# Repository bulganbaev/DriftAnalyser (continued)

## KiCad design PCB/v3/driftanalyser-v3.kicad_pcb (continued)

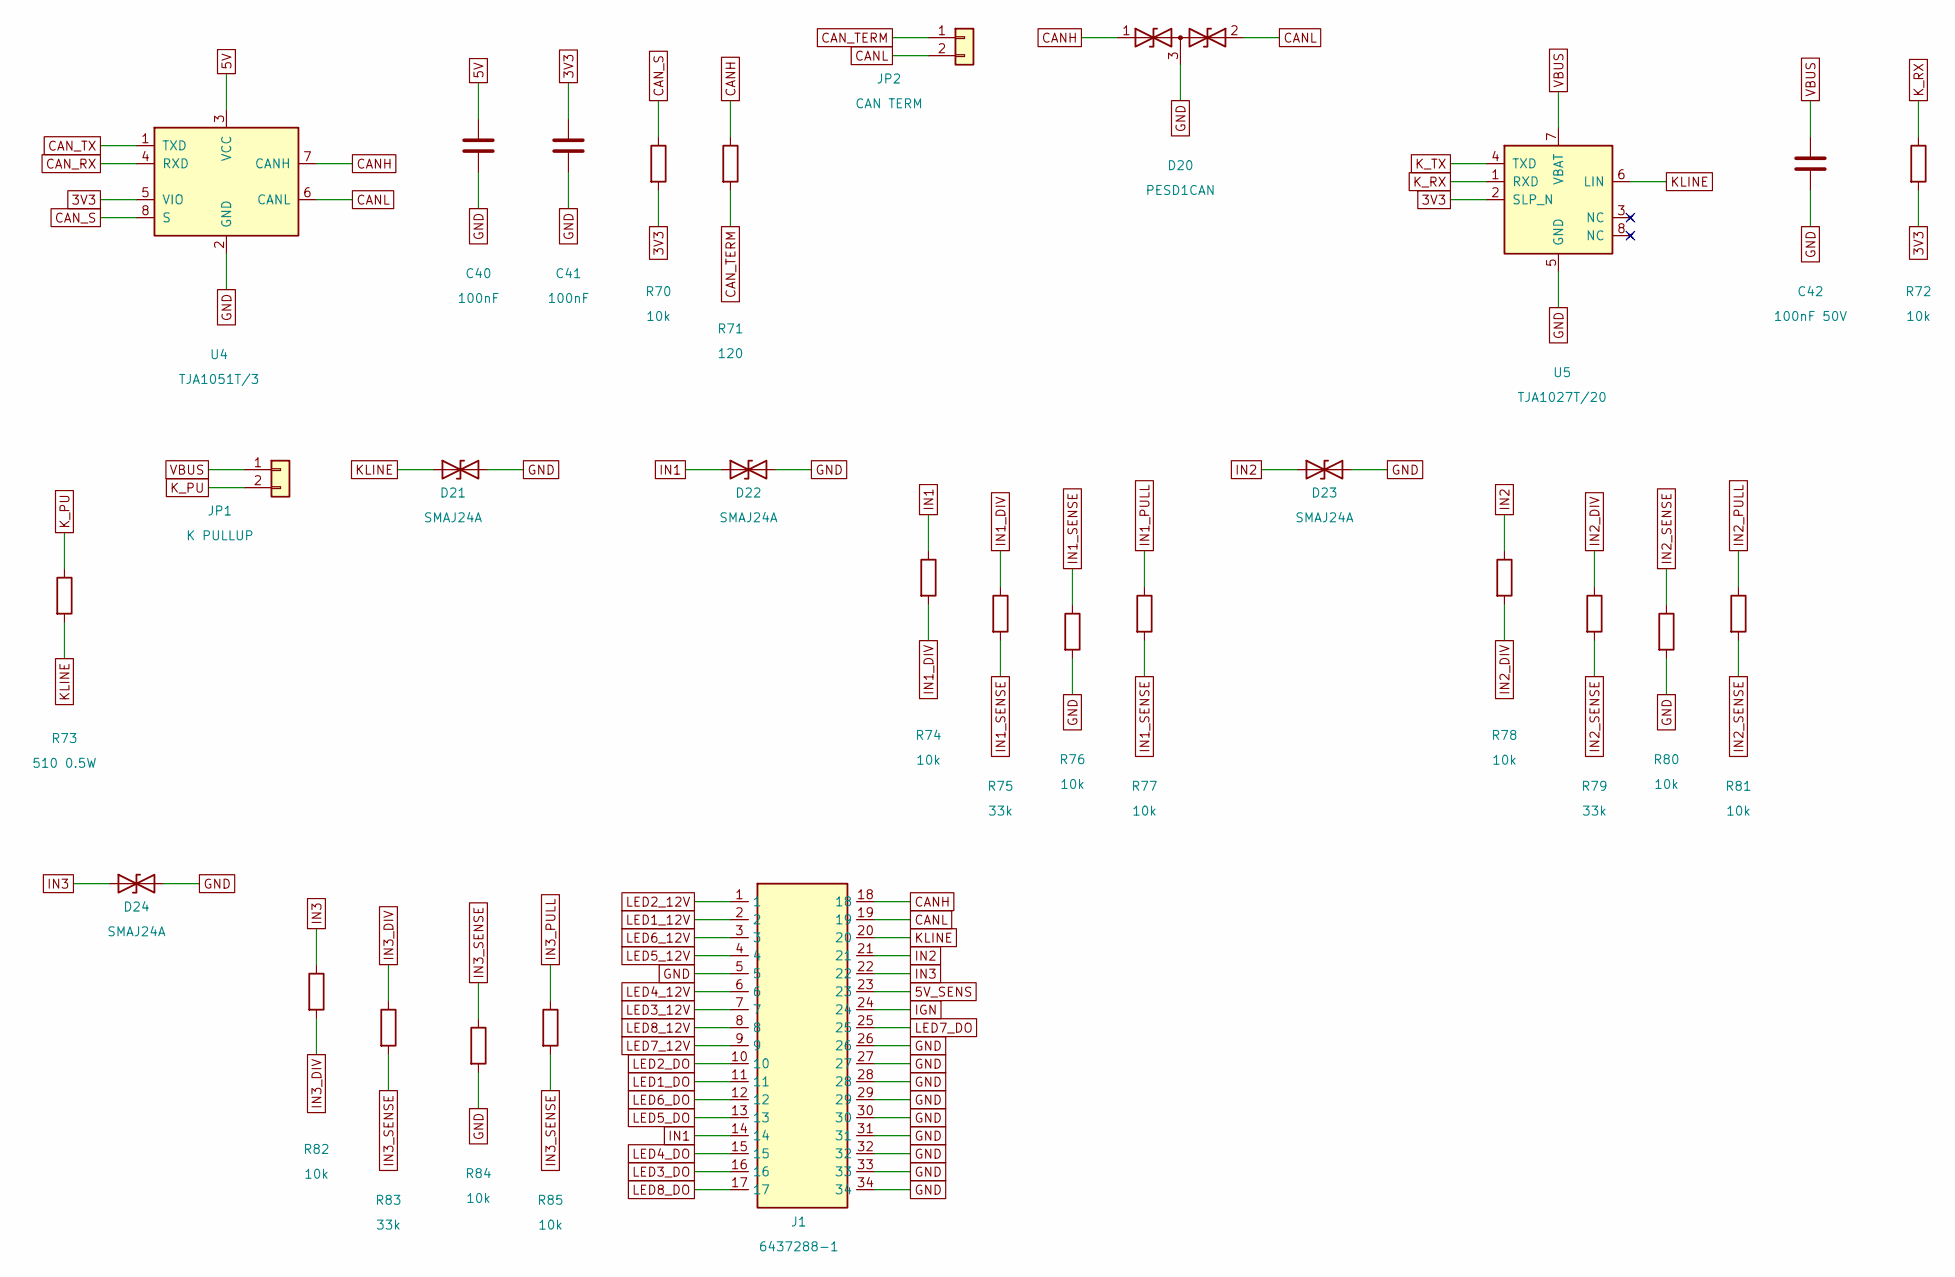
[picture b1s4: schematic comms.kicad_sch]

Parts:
C40, C41: 100nF; C_0603_1608Metric; MPN CC0603KRX7R9BB104; LCSC C14663
C42: 100nF 50V; C_0603_1608Metric; MPN CC0603KRX7R9BB104; LCSC C14663
D20: PESD1CAN; SOT-23; MPN PESD1CAN,215; LCSC C15771
D21, D22, D23, D24: SMAJ24A; D_SMA; MPN SMAJ24A; LCSC C148222
J1: 6437288-1; TE_6437288-1; MPN 6437288-1; LCSC C574787
JP1: K PULLUP; PinHeader_1x02_P2.54mm_Vertical; MPN PZ254V-11-02P; LCSC C492401
JP2: CAN TERM; PinHeader_1x02_P2.54mm_Vertical; MPN PZ254V-11-02P; LCSC C492401
R70, R72, R74, R76, R77, R78, R80, R81, R82, R84, R85: 10k; R_0603_1608Metric; MPN 0603WAF1002T5E; LCSC C25804
R71: 120; R_1206_3216Metric; MPN 1206W4F1200T5E; LCSC C17909
R73: 510 0.5W; R_2512_6332Metric; MPN FRC2512J511TS; LCSC C2934121
R75, R79, R83: 33k; R_0603_1608Metric; MPN 0603WAF3302T5E; LCSC C4216
U4: TJA1051T/3; SOIC-8_3.9x4.9mm_P1.27mm; MPN TJA1051T/3,118; LCSC C58988
U5: TJA1027T/20; SOIC-8_3.9x4.9mm_P1.27mm; MPN TJA1027T/20,118; LCSC C112994

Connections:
3V3: C41.1, R70.2, R72.2, U4.5 (VIO), U5.2 (SLP_N); also elsewhere on the board
5V: C40.1, U4.3 (VCC); also elsewhere on the board
5V_SENS: J1.23; also elsewhere on the board
CANH: D20.1 (A1), J1.18, R71.1, U4.7 (CANH)
CANL: D20.2 (A2), J1.19, JP2.2, U4.6 (CANL)
CAN_RX: U4.4 (RXD); also elsewhere on the board
CAN_S: R70.1, U4.8 (S); also elsewhere on the board
CAN_TERM: JP2.1, R71.2
CAN_TX: U4.1 (TXD); also elsewhere on the board
GND: C40.2, C41.2, C42.2, D20.3 (common), D21.2 (A2), D22.2 (A2), D23.2 (A2), D24.2 (A2), J1.5, J1.26, J1.27, J1.28, J1.29, J1.30, J1.31, J1.32, J1.33, J1.34, R76.2, R80.2, R84.2, U4.2 (GND), U5.5 (GND); also elsewhere on the board
IGN: J1.24; also elsewhere on the board
IN1: D22.1 (A1), J1.14, R74.1
IN1_DIV: R74.2, R75.1
IN1_PULL: R77.1; also elsewhere on the board
IN1_SENSE: R75.2, R76.1, R77.2; also elsewhere on the board
IN2: D23.1 (A1), J1.21, R78.1
IN2_DIV: R78.2, R79.1
IN2_PULL: R81.1; also elsewhere on the board
IN2_SENSE: R79.2, R80.1, R81.2; also elsewhere on the board
IN3: D24.1 (A1), J1.22, R82.1
IN3_DIV: R82.2, R83.1
IN3_PULL: R85.1; also elsewhere on the board
IN3_SENSE: R83.2, R84.1, R85.2; also elsewhere on the board
KLINE: D21.1 (A1), J1.20, R73.2, U5.6 (LIN)
K_PU: JP1.2, R73.1
K_RX: R72.1, U5.1 (RXD); also elsewhere on the board
K_TX: U5.4 (TXD); also elsewhere on the board
LED1_12V: J1.2; also elsewhere on the board
LED1_DO: J1.11; also elsewhere on the board
LED2_12V: J1.1; also elsewhere on the board
LED2_DO: J1.10; also elsewhere on the board
LED3_12V: J1.7; also elsewhere on the board
LED3_DO: J1.16; also elsewhere on the board
LED4_12V: J1.6; also elsewhere on the board
LED4_DO: J1.15; also elsewhere on the board
LED5_12V: J1.4; also elsewhere on the board
LED5_DO: J1.13; also elsewhere on the board
LED6_12V: J1.3; also elsewhere on the board
LED6_DO: J1.12; also elsewhere on the board
LED7_12V: J1.9; also elsewhere on the board
LED7_DO: J1.25; also elsewhere on the board
LED8_12V: J1.8; also elsewhere on the board
LED8_DO: J1.17; also elsewhere on the board
VBUS: C42.1, JP1.1, U5.7 (VBAT); also elsewhere on the board

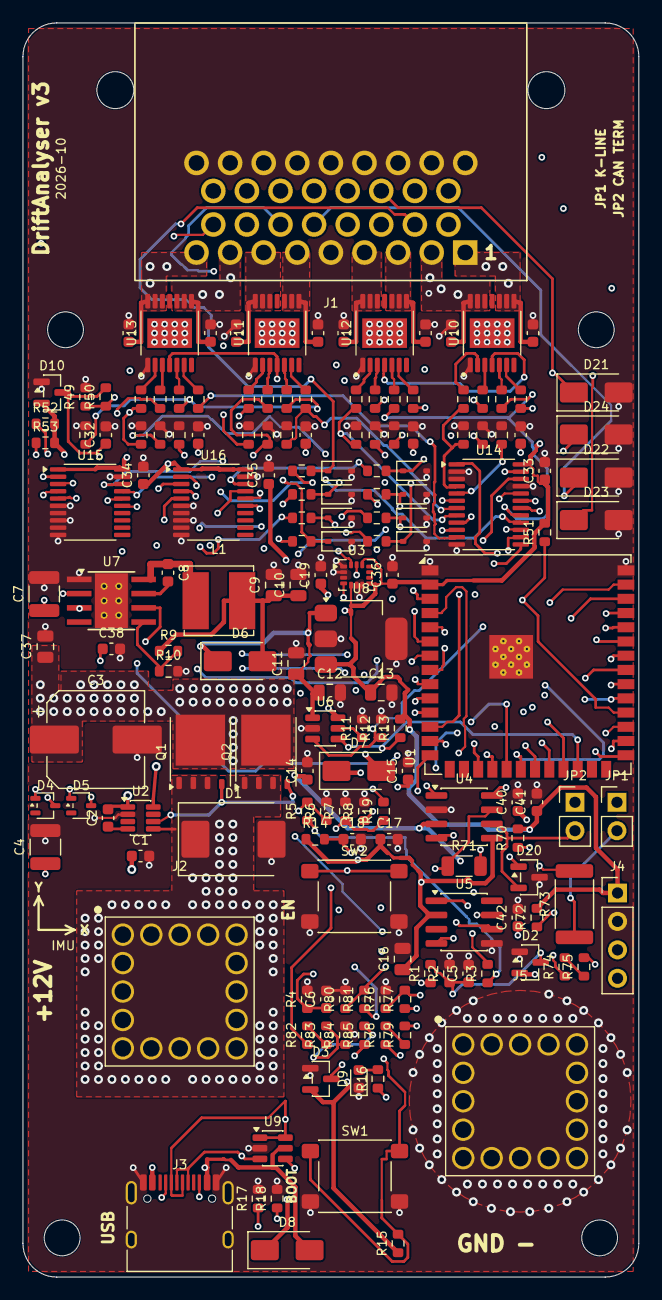
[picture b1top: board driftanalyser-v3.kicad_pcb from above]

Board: 6 copper layers, 55.0 x 112.0 mm, 173 parts (0 on the bottom side), 124 nets.

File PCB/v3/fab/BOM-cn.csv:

型号/值,位号,封装,单套数量,立创编号,厂家型号,厂家
100nF 50V,"C1,C42",C_0603_1608Metric,2,C14663,CC0603KRX7R9BB104,YAGEO
220nF 25V,C2,C_0603_1608Metric,1,C21120,CL10B224KA8NNNC,Samsung Electro-Mechanics
100uF 50V,C3,CP_Elec_8x10.5,1,C2983550,GVZ1H107M0810CNVC,HRK
10uF 50V,"C4,C7",C_1210_3225Metric,2,C2918502,CS3225X7R106K500NRL,SAMWHA
100nF,"C5,C6,C8,C14,C17,C19,C20,C23,C26,C29,C33,C34,C35,C36,C40,C41",C_0603_1608Metric,16,C14663,CC0603KRX7R9BB104,YAGEO
22uF 10V,"C9,C10,C11,C16",C_0805_2012Metric,4,C45783,CL21A226MAQNNNE,Samsung Electro-Mechanics
10uF,"C12,C13",C_0805_2012Metric,2,C15850,CL21A106KAYNNNE,Samsung Electro-Mechanics
1uF,"C15,C18,C38",C_0603_1608Metric,3,C15849,CL10A105KB8NNNC,Samsung Electro-Mechanics
10nF 50V,"C21,C22,C24,C25,C27,C28,C30,C31",C_0603_1608Metric,8,C57112,0603B103K500NT,FH
10nF,C32,C_0603_1608Metric,1,C57112,0603B103K500NT,FH
220nF 100V,C37,C_0805_2012Metric,1,C513710,CC0805KKX7R0BB224,YAGEO
SMCJ24CA,D1,D_SMC,1,C151279,SMCJ24CA,Littelfuse
BAT54S,"D2,D3,D10",SOT-23,3,C47546,"BAT54S,215",Nexperia
BAT54W,"D4,D5",SOT-323_SC-70,2,C77328,BAT54W,JSCJ
SS34,"D6,D7,D8",D_SMA,3,C8678,SS34,MDD
GREEN,D9,LED_0603_1608Metric,1,C22371299,PSC-1608U49GC-G4,HONGLITRONIC
PESD5V0S1BA,"D11,D12,D13,D14,D15,D16,D17,D18",D_SOD-323,8,C19224,"PESD5V0S1BA,115",Nexperia
PESD1CAN,D20,SOT-23,1,C15771,"PESD1CAN,215",Nexperia
SMAJ24A,"D21,D22,D23,D24",D_SMA,4,C148222,SMAJ24A,Littelfuse
6437288-1,J1,TE_6437288-1,1,C574787,6437288-1,TE Connectivity
7461059 M6,"J2,J5",Wurth_REDCUBE_7461059,2,,7461059 (hand-fit),Wurth
USB-C 16P,J3,USB_C_Receptacle_HRO_TYPE-C-31-M-12,1,C2765186,TYPE-C 16PIN 2MD(073),SHOU HAN
UART0,J4,PinHeader_1x04_P2.54mm_Vertical,1,C2691448,PZ254V-11-04P,XFCN
K PULLUP,JP1,PinHeader_1x02_P2.54mm_Vertical,1,C492401,PZ254V-11-02P,XFCN
CAN TERM,JP2,PinHeader_1x02_P2.54mm_Vertical,1,C492401,PZ254V-11-02P,XFCN
10uH,L1,L_Bourns_SRN6045TA,1,C2046332,SRN6045TA-100M,Bourns
BSC016N06NS,"Q1,Q2",Infineon_TDSON-8_FL,2,C454269,BSC016N06NS,Infineon
470k,R1,R_0603_1608Metric,1,C23178,0603WAF4703T5E,UNI-ROYAL
100k,"R2,R3,R5,R7,R9,R13,R19",R_0603_1608Metric,7,C25803,0603WAF1003T5E,UNI-ROYAL
47k,R4,R_0603_1608Metric,1,C25819,0603WAF4702T5E,UNI-ROYAL
33k,"R6,R75,R79,R83",R_0603_1608Metric,4,C4216,0603WAF3302T5E,UNI-ROYAL
10k,"R8,R12,R14,R15,R20,R22,R24,R26,R28,R30,R32,R34,R36,R37,R40,R43,R46,R51,R70,R72,R74,R76,R77,R78,R80,R81,R82,R84,R85",R_0603_1608Metric,29,C25804,0603WAF1002T5E,UNI-ROYAL
22.6k,R10,R_0603_1608Metric,1,C100874,CR0603FA2262G,LIZ Elec
210k,R11,R_0603_1608Metric,1,C22952,0603WAF2103T5E,UNI-ROYAL
1k,R16,R_0603_1608Metric,1,C21190,0603WAF1001T5E,UNI-ROYAL
5.1k,"R17,R18",R_0603_1608Metric,2,C23186,0603WAF5101T5E,UNI-ROYAL
4.7k,"R21,R23,R25,R27,R29,R31,R33,R35,R38,R39,R41,R42,R44,R45,R47,R48,R50,R52,R53",R_0603_1608Metric,19,C23162,0603WAF4701T5E,UNI-ROYAL
1.2k,R49,R_0603_1608Metric,1,C22765,0603WAF1201T5E,UNI-ROYAL
33,"R54,R55,R56,R57,R58,R59,R60,R61",R_0603_1608Metric,8,C23140,0603WAF330JT5E,UNI-ROYAL
120,R71,R_1206_3216Metric,1,C17909,1206W4F1200T5E,UNI-ROYAL
510 0.5W,R73,R_2512_6332Metric,1,C2934121,FRC2512J511TS,FOJAN
BOOT,SW1,SW_SPST_PTS645Sx43SMTR92,1,C221880,PTS645SM43SMTR92LFS,C&K
EN,SW2,SW_SPST_PTS645Sx43SMTR92,1,C221880,PTS645SM43SMTR92LFS,C&K
ESP32-S3-WROOM-1U-N16R2,U1,ESP32-S3-WROOM-1U,1,C3013945,ESP32-S3-WROOM-1U-N16R2,Espressif
LM74700-Q1,U2,SOT-23-8,1,C3236229,LM74700QDDFRQ1,Texas Instruments
LSM6DS3TR-C,U3,LGA-14_3x2.5mm_P0.5mm_LayoutBorder3x4y,1,C967633,LSM6DS3TR-C,STMicroelectronics
TJA1051T/3,U4,SOIC-8_3.9x4.9mm_P1.27mm,1,C58988,"TJA1051T/3,118",NXP
TJA1027T/20,U5,SOIC-8_3.9x4.9mm_P1.27mm,1,C112994,"TJA1027T/20,118",NXP
TPS2553DBV,U6,SOT-23-6,1,C55266,TPS2553DBVR,Texas Instruments
LMR36520ADDAR,U7,Texas_HTSOP-8-1EP_3.9x4.9mm_P1.27mm_EP2.95x4.9mm_Mask2.4x3.1mm_ThermalVias,1,C2879422,LMR36520ADDAR,Texas Instruments
AP7361C-33E,U8,SOT-223-3_TabPin2,1,C500795,AP7361C-33E-13,Diodes Incorporated
USBLC6-2SC6,U9,SOT-23-6,1,C7519,USBLC6-2SC6,STMicroelectronics
BTS7008-2EPA,"U10,U11,U12,U13",PG-TSDSO-14,4,C534830,BTS7008-2EPA,Infineon
PCA9555PW,U14,TSSOP-24_4.4x7.8mm_P0.65mm,1,C128392,"PCA9555PW,118",NXP
74HCT245PW,"U15,U16",TSSOP-20_4.4x6.5mm_P0.65mm,2,C5980,"74HCT245PW,118",Nexperia

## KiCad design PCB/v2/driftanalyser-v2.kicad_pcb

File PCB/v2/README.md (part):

# DriftAnalyser PCB v2

Вторая ревизия платы. Дизайн сгенерирован из `gen/model.py` + `gen/placement.py`
скриптом (`gen/build.sh`), сам KiCad-проект (`driftanalyser-v2.kicad_pro` и
остальные `.kicad_*` в этой папке) — результат генерации, руками там лучше не лазить,
следующий пересбор всё затрёт. Fab-файлы под заказ в `fab/`, там же
`fab/README-fab.md` с опциями заказа у JLC и что проверить в руки перед подачей питания
первый раз — читать вместе с этим файлом, не дублирую здесь.

## Что это и чем отличается от v1

Старая плата (`PCB/`, EasyEDA-схема) сейчас стоит в машине, её README живёт в корне
репозитория. У неё врождённые проблемы: 7805 не тянет ленты, MPU-6050 с недорисованной
обвязкой, перепутанная шелкография LED3/LED5, клеммники 3.81, неиспользуемые реле/GPS.
v2 — не патч, а плата с нуля под реальное применение (12В ленты WS2815 на дрифт-машине
с CAN/K-line от BMW MS43):

- **Только 12В ленты.** 5В части на плате больше нет вообще — ни линейника 7805, ни
  разъёма под 5В ленту. Кто хочет 5В ленту — питает её внешним DC-DC, на разъём заводит
  только DATA/GND (как и раньше на v1, только теперь это единственный вариант).
- Силовой ключ лент — Infineon **BTS7002-1EPP** (PROFET+2, встроенная защита от КЗ,
  перегрева, обратки, аналоговый выход тока IS) вместо голого реле/транзистора.
- CAN-трансивер **TJA1051T/3** (3.3В логика, вместо TJA1050 + сдвигателей уровня на v1).
- Добавлен K-line трансивер **TJA1027T/20** (LIN-совместимый) — v1 K-line вообще не умела,
  диагностика MS43 по K-line была недоступна.
- IMU заменён на **LSM6DS3TR-C** (MPU-6050 снят с производства, на рынке в основном контрафакт).
- Убрано: реле×2, посадочное место GPS NEO-6M, TXB0108, 7805, AMS1117, клеммники 3.81мм —
  ничего из этого не использовалось в прошивке или работало плохо.
- Разъёмы питания и лент поменялись: XT60PW вместо клеммника, JST VH 3-пин на ленту
  (12V/DATA/GND) вместо клеммника с перемычками выбора напряжения.
- Плата **4-слойная**, 110×75мм, JLC04161H-7628 1.6мм (спека изначально предполагала
  2 слоя — при трассировке 20А силовой шины на двух слоях не хватало места и трассы
  ужимались в опасно узкие коридоры, перешли на 4 слоя: In1 сплошная земля, In2 — VBAT
  и 12V_LED полигоны, см. "Питание и пределы" ниже).
- Прошивка **пока не тронута** и таргетится на v1 — карта пинов, драйвер IMU и всё
  остальное под v2 не написаны, см. "Что осталось руками" ниже.

## Как пересобрать

```
bash PCB/v2/gen/build.sh
```

Пересобирает всё по порядку: схему из `gen/model.py`, плату и расстановку из
`gen/placement.py`, трассировку, DRC/ERC, экспорт в `fab/`, прогоняет тесты
(`gen/tests`).

Требования:
- KiCad 10, установлен в `/Applications` (`build.sh` дёргает питон прямо из
  `KiCad.app/Contents/Frameworks/Python.framework/...`, кастомный путь в системе не подхватится).
- Java для Freerouting: `/opt/homebrew/opt/openjdk/bin/java` (переопределяется переменной
  `JAVA`). Freerouting 2.4.1 хочет Java ≥25, системный `/usr/bin/java` на macOS обычно старее.
- Freerouting jar в `~/.local/freerouting/freerouting.jar`.

**Трассировка не гоняется на каждой пересборке** — она реплеится из закоммиченного
`fab/route.ses`. `DA2_REROUTE=1` просит у Freerouting новый прогон: он недетерминирован
(порядок объектов, не фиксированный seed), результат может отличаться от того что в
репозитории и может оставить открытые связи — если рероутишь, проверяй DRC-отчёт заново.
Треки и переходные, которые билдер рисует руками **до** импорта SES, реплей затирает —
переживают только шаги **после** импорта (например `vbat_stitch`, который доливает
переходные в VBAT-полигон уже после трассировки).

Тяжёлый экспорт (STEP, 3D-рендеры) — под `DA2_HEAVY=1` (в `build.sh` включено по
умолчанию), в git не лежит.

Что реально меняется в git при пересборке неизменной платы:
- `driftanalyser-v2.kicad_pcb` — **меняется каждый раз**. `pcbnew` выдаёт каждому
  посадочному месту случайный KIID, порядок объектов в файле от него зависит, так
  что диф есть даже когда геометрия та же. Это шум, а не изменение платы.
- `fab/render-top.svg` и `fab/gerbers.zip` — **меняются вместе с ним**: порядок
  элементов в SVG и порядок вспышек в герберах идут из порядка объектов в плате.
  Времени в них больше нет: SVG получает фиксированный `<title>`, а в zip даты
  (`TF.CreationDate` в каждом гербере, в обоих `.drl` и в `.gbrjob`, плюс
  человекочитаемый `G04 Created by KiCad ... date`) подменяются на фиксированные
  при упаковке. Прогнать `gen.export` дважды по одной и той же плате — архив
  побайтово одинаковый; на диске в `fab/gerbers/` (не трекается) дата настоящая,
  это метка фаба.
- Остальные трекнутые артефакты (`netlist.net`, `erc.rpt`, `drc*.json`,
  `BOM.csv`, `CPL.csv`, `README-fab.md`, `schematic.pdf`) стабильны — тесты
  (`pytest gen/tests`) не пачкают ни один трекнутый файл.

Изменения вносить в `gen/model.py` (детали, пины, номиналы) и `gen/placement.py`
(расположение) — не в сгенерённых `.kicad_sch`/`.kicad_pcb` напрямую, их перезатрёт
следующий `build.sh`.

## Разъёмы и распиновки

| Разъём | Тип | Пины |
|---|---|---|
| J1 PWR | XT60PW-M | 1 GND, **2 +12V** (левая дырка если смотреть на разъём, «+» на шелкографии — см. предупреждение ниже) |
| J11..J16 LED1..LED6 | JST VH B3P-VH 3-пин | 1 12V, 2 DATA, 3 GND |
| J6 OBD | JST XH 4-пин | 1 CANH, 2 CANL, 3 K, 4 GND |
| J2 USB | USB-C 16-пин | нативный USB на ESP32-S3 (D+/D- GPIO20/19) |
| J3 UART0 | 1×4 header 2.54мм | 1 3V3, 2 GND, 3 TX (GPIO43), 4 RX (GPIO44) — аварийная прошивка через UART |
| J4 EXT | 1×6 header 2.54мм | 1 3V3, 2 GND, 3 TX2 (GPIO35), 4 RX2 (GPIO36), 5 SDA (GPIO8), 6 SCL (GPIO9) — под будущую телеметрию |
| J5 microSD | push-pull с детектом карты (Hirose DM3BT-DSF-PEJS), SDMMC 4-бит | карта вынимается пальцами, не нажатием; CD на GPIO48. Не задействован в прошивке |

J3/J4 стоят справа от ESP32 (x≈29.5/35мм, y 20..36мм) — не в углу платы, как можно
подумать по старой привычке от v1.

**Полярность XT60PW проверена по геометрии в библиотеке KiCad и конвенции AMASS/XT60
(скошенный торец корпуса — минус, прямой — плюс), но не по живому разъёму. Перед первым
включением прозвонить тестером конкретную пару XT60, которая пойдёт в машину** — не
поленись, а то спалишь плату на первой секунде.

## Джамперы

- **JP1 CAN TERM** — 120 Ом между CANH/CANL. Снять, если плата подключается к готовой
  шине машины (там свои терминаторы, MS43 в частности). Ставить, только если плата —
  физический конец CAN-шины.
- **JP2 K PULLUP** — 510 Ом 0.5Вт от K-line к VBAT (тестерная подтяжка по ISO 9141).
  Ставить, если ECU сам не подтягивает линию K. У большинства ECU подтяжка своя —
  джампер обычно снят, пробовать без него сначала.

## Подключение WS2815

- У WS2815 4 провода на пиксель (5В/12В, GND, DATA, BI — backup-in, резервная линия
  для детекта обрыва данных), а на плате разъём **3-пиновый** (12V/DATA/GND). BI на
  разъём не выведен — подключается прямо **на самой ленте**, у первого пикселя,
  замыкается на GND. Без этого лента может не стартовать вообще (у WS2815 есть
  автоматический детект обрыва по BI).
- Подключать разъём к **началу** ленты (input end), не к середине и не к хвосту —
  иначе адресация светодиодов в прошивке не совпадёт с физикой.
- Сечение проводов от разъёма до ленты: питание 1.0–1.5 мм², данные 0.5 мм² хватает
  с запасом.
- До ~2м ленты 144/м на один разъём — дальше просадка по длине и ток на контакте JST
  VH (рейтинг 10А/пин) уже неприятный.

## Питание и пределы

- Вход 9–16В штатно, XT60PW. TVS D1 (SMDJ18A) на VBAT держит броски. 3S LiPo — ок,
  4S/6S — нет, слишком высокое напряжение для линейки лент/буков.
- Предохранитель — **один, 30А, в жгуте у аккумулятора**, не на плате. Каналы лент
  защищает сам BTS7002-1EPP (тепловое отключение + авторестарт встроены в чип), IS
  выведен в прошивку через GPIO2 (ADC), но само чтение и программный латч по IS ещё
  не написаны — см. "Что осталось руками".
- **Continuous rating по силовой шине VBAT/12V — 20А**, это потолок, который держит
  посадка ключа BTS7002 (тепловое сопротивление корпуса/пятака), и это же — самое
  узкое сечение всей платы: VBAT-коридор под ESP/буком, 20.0А в самом худшем срезе.
  Запаса там почти нет, это край допуска, а не комфортная цифра.
- **Эта цифра держится только если при заказе у JLC явно выбрать 1 oz inner copper**
  (не дефолт для 4-слойной платы — дефолт 0.5 oz). На дефолтной 0.5 oz внутренняя медь
  VBAT-коридор садится примерно вдвое, до ~12А — с ключом на 20А номинальных это уже
  не запас, а прямой путь погреть плату. Подробности и цифры по остальным силовым
  дорожкам — в `fab/README-fab.md`.

## Карта GPIO

Пины по факту разведённой платы (сверено с `gen/model.py`, U1 = ESP32-S3-WROOM-1-N16R2):

| GPIO | Назначение | Заметка |
|---|---|---|
| 0 | BOOT | strapping |
| 1 | VBAT_SENSE | ADC1, делитель 47k/10k |
| 2 | LED_ISENSE | ADC1, выход IS ключа BTS7002 |
| 4 | LED1 DATA | → 74HCT245 A1 → JST VH pin2 |
| 5 | LED2 DATA | → 74HCT245 A2 |
| 6 | LED3 DATA | → 74HCT245 A3 |
| 7 | LED4 DATA | → 74HCT245 A4 |
| 15 | LED5 DATA | → 74HCT245 A5 |
| 16 | LED6 DATA | → 74HCT245 A6 |
| 8 | I2C SDA | IMU + разъём EXT (pin5) |
| 9 | I2C SCL | IMU + разъём EXT (pin6) |
| 10 | LED_PWR_EN | → BTS7002 IN, подтянут вниз 10k (ленты выключены пока прошивка не включит) |
| 11 | STATUS_LED | |
| 12 | K_RX | UART1, TJA1027 RXD |
| 13 | K_TX | UART1, TJA1027 TXD |
| 14 | CAN_STB | → TJA1051 S |
| 17 | IMU_INT1 | |
| 18 | CAN_TX | → TJA1051 TXD |
| 19 / 20 | USB D- / D+ | нативный USB |
| 21 | CAN_RX | ← TJA1051 RXD |
| 35 / 36 | UART2 TX / RX | разъём EXT (pin3/4) |
| 38 / 39 / 40 / 41 / 42 | SD CMD / CLK / D0 / D1 / D2 | SDMMC 4-бит, подтяжки 10k |
| 47 | SD D3 | подтяжка 10k |
| 48 | SD_CD | card detect |
| 43 / 44 | UART0 TX / RX | разъём J3 |
| 3, 45, 46 | не используются | strapping, оставлены свободными |

### Ориентация IMU

U5 (LSM6DS3TR-C) стоит без поворота (rot 0), pad 1 — левый верхний, то есть как
на виде сверху из даташита. Значит оси сенсора в системе платы:

- **+X сенсора → правый край платы** (x = 110). По прошивке это **нос машины**.
- **+Y сенсора → верхний край платы** (y = 0), там где ленточные разъёмы.
- **+Z сенсора → вверх из лицевой меди**, то есть из крышки корпуса.

Оси подписаны на шелкографии рядом с U5. Плату в машине ставить лицом вверх и
правым краем вперёд — иначе знаки в прошивке придётся переставлять.

## Корпус

`enclosure/enclosure.py`, CadQuery в `enclosure/.venv` (Python 3.11):

```
enclosure/.venv/bin/python enclosure/enclosure.py
```

→ `enclosure/out/{base,lid}.stl`, `enclosure/out/enclosure.step`. Флаг `--parts`
дополнительно рисует тела компонентов по отдельности (удобно проверять клиренсы).

Параметры собраны в начале файла: стенка 2.4мм, дно 2мм, стойки под M3 (4.0мм
отверстие под термовставку либо 2.5мм под саморез в пластик), крышка на защёлках
(snap-fit), уши под винты 4мм, вентиляционные прорези над горячей зоной (BTS7002,
буковский/LDO участок).

Крепёж: четыре M3 (∅3.2мм) по углам платы, в координатах платы (x вправо, y вниз
от левого верхнего угла, мм) — **(4, 4), (106, 4), (4, 71), (106, 71)**. Стойки в
базе корпуса стоят ровно под ними (`placement.HOLES`).

Защёлки крышки: по две на длинных стенках и по одной на коротких. На стенке с
ленточными разъёмами прорези под провода идут шириной 16мм с шагом 15.3мм, то
есть сливаются в одну щель от x≈11 до x≈103 — места между разъёмами нет, поэтому
обе защёлки этой стенки сидят по её краям (x = 2 и x = 107, вторая укорочена до
5мм).

## Что осталось руками / известные ограничения

- Прошивка под v2 — ветка `fw-v2` (пины, LSM6DS3TR-C, ключ лент с латчем по IS, VBAT,
  K-line DS2). Не сделано: microSD, IMU_INT1.
- **Все разъёмы, кроме XT60, вертикальные** (top-entry). Корпус `enclosure.py` считал только
  высоту колодки (`COMP_H = 12`), с вставленной фишкой и проводом крышка не закрывается.
  В v2.1 ставить боковые S3P-VH / S4B-XH-A.
- GNSS/RTK телеметрия — отдельный проект и отдельное железо, на этой плате только
  разъём EXT (см. таблицу разъёмов) для связи с ней.
- XT60 полярность выверена по библиотеке, не по живому разъёму — прозвонить перед
  первым включением (см. предупреждение выше).
- VBAT-коридор держит заявленные 20А только при явном выборе 1 oz inner copper при
  заказе у JLC — дефолт этот минимум срезает почти вдвое (см. "Питание и пределы").
- Посадочные места ESP32-модуля используют термопереходные 0.2мм — у JLC это
  доплата (min hole 0.2мм), у остального на плате 0.4мм и крупнее.
- IMU LSM6DS3TR-C в корпусе LGA-14, шаг 0.5мм, под ним clearance-правило 0.15мм —
  самое мелкое место на плате. Руками паяется тяжело, ENIG в качестве финишного
  покрытия облегчает (см. `fab/README-fab.md`).
- Всё, что Freerouting не дотрассировал автоматически — ничего: закоммиченный
  `fab/route.ses` даёт полностью разведённую плату (0 DRC violations, 0
  unconnected items, 0 schematic parity). Но пересборка с `DA2_REROUTE=1` может
  оставить открытые связи заново — тогда список будет в выводе `gen.route`,
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
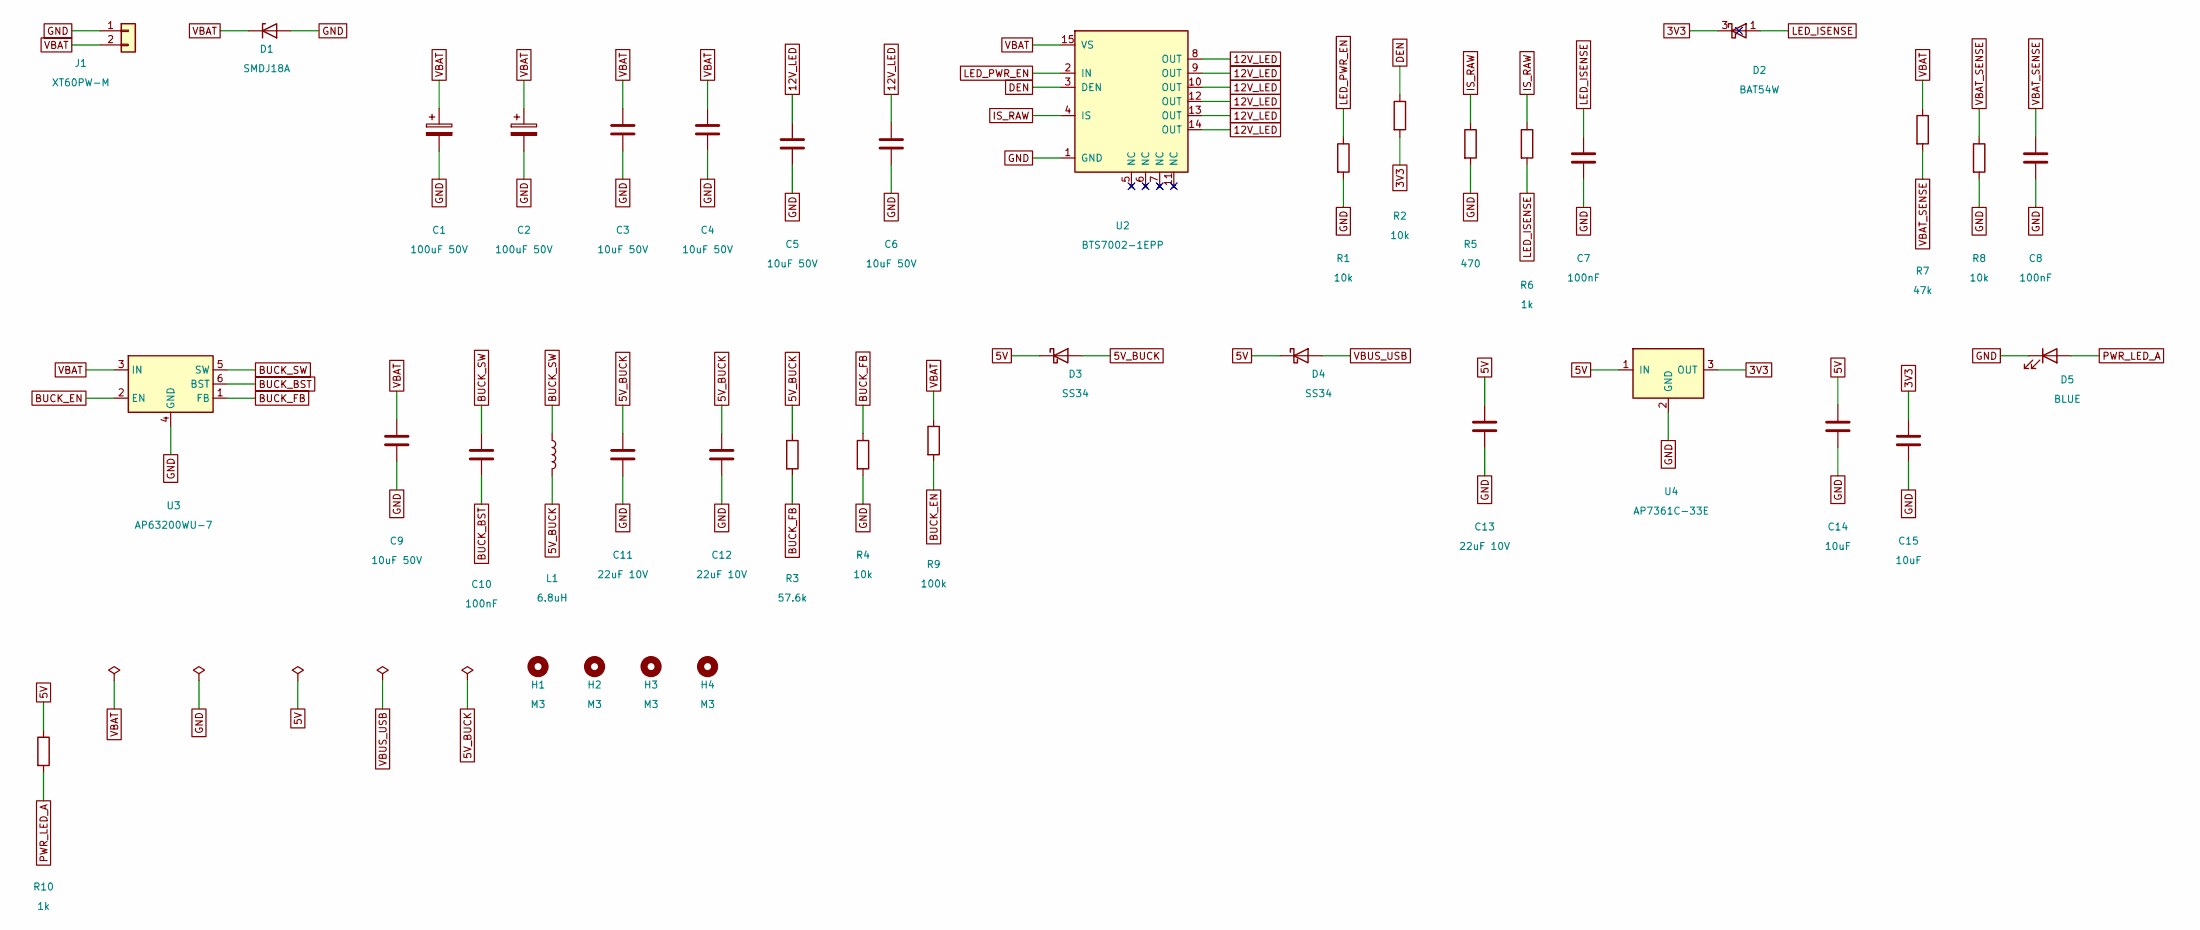
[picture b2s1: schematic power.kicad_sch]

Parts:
C1, C2: 100uF 50V; CP_Elec_8x10.5; MPN GVZ1H107M0810CNVC; LCSC C2983550
C3, C4, C5, C6, C9: 10uF 50V; C_1210_3225Metric; MPN CS3225X7R106K500NRL; LCSC C2918502
C7, C8, C10: 100nF; C_0603_1608Metric; MPN CC0603KRX7R9BB104; LCSC C14663
C11, C12, C13: 22uF 10V; C_0805_2012Metric; MPN CL21A226MAQNNNE; LCSC C45783
C14, C15: 10uF; C_0805_2012Metric; MPN CL21A106KAYNNNE; LCSC C15850
D1: SMDJ18A; D_SMC; MPN 5.0SMDJ18A; LCSC C284071
D2: BAT54W; SOT-323_SC-70; MPN BAT54W; LCSC C77328
D3, D4: SS34; D_SMA; MPN SS34; LCSC C8678
D5: BLUE; LED_0603_1608Metric; MPN XL-1608UBC-04; LCSC C965807
H1, H2, H3, H4: M3; MountingHole_3.2mm_M3
J1: XT60PW-M; AMASS_XT60PW-M_1x02_P7.20mm_Horizontal; MPN XT60PW-M; LCSC C98732
L1: 6.8uH; L_Bourns_SRN6045TA; MPN YNR6045-6R8M; LCSC C341066
R1, R2, R4, R8: 10k; R_0603_1608Metric; MPN 0603WAF1002T5E; LCSC C25804
R3: 57.6k; R_0603_1608Metric; MPN FRC0603F5762TS; LCSC C2933240
R5: 470; R_0603_1608Metric; MPN 0603WAF4700T5E; LCSC C23179
R6, R10: 1k; R_0603_1608Metric; MPN 0603WAF1001T5E; LCSC C21190
R7: 47k; R_0603_1608Metric; MPN 0603WAF4702T5E; LCSC C25819
R9: 100k; R_0603_1608Metric; MPN 0603WAF1003T5E; LCSC C25803
U2: BTS7002-1EPP; PG-TSDSO-14; MPN BTS70021EPPXUMA1; LCSC C2680407
U3: AP63200WU-7; TSOT-23-6; MPN AP63200WU-7; LCSC C2071868
U4: AP7361C-33E; SOT-223-3_TabPin2; MPN AP7361C-33E-13; LCSC C500795

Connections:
3V3: C15.1, D2.3 (K), R2.2, U4.3 (OUT); also elsewhere on the board
5V: C13.1, C14.1, D3.1 (K), D4.1 (K), R10.1, U4.1 (IN); also elsewhere on the board
5V_BUCK: C11.1, C12.1, D3.2 (A), L1.2, R3.1
12V_LED: C5.1, C6.1, U2.8 (OUT), U2.9 (OUT), U2.10 (OUT), U2.12 (OUT), U2.13 (OUT), U2.14 (OUT); also elsewhere on the board
BUCK_BST: C10.2, U3.6 (BST)
BUCK_EN: R9.2, U3.2 (EN)
BUCK_FB: R3.2, R4.1, U3.1 (FB)
BUCK_SW: C10.1, L1.1, U3.5 (SW)
DEN: R2.1, U2.3 (DEN)
GND: C1.2, C2.2, C3.2, C4.2, C5.2, C6.2, C7.2, C8.2, C9.2, C11.2, C12.2, C13.2, C14.2, C15.2, D1.2 (A), D5.1 (K), J1.1, R1.2, R4.2, R5.2, R8.2, U2.1 (GND), U3.4 (GND), U4.2 (GND); also elsewhere on the board
IS_RAW: R5.1, R6.1, U2.4 (IS)
LED_ISENSE: C7.1, D2.1 (A), R6.2; also elsewhere on the board
LED_PWR_EN: R1.1, U2.2 (IN); also elsewhere on the board
PWR_LED_A: D5.2 (A), R10.2
VBAT: C1.1, C2.1, C3.1, C4.1, C9.1, D1.1 (K), J1.2, R7.1, R9.1, U2.15 (VS), U3.3 (IN); also elsewhere on the board
VBAT_SENSE: C8.1, R7.2, R8.1; also elsewhere on the board
VBUS_USB: D4.2 (A); also elsewhere on the board

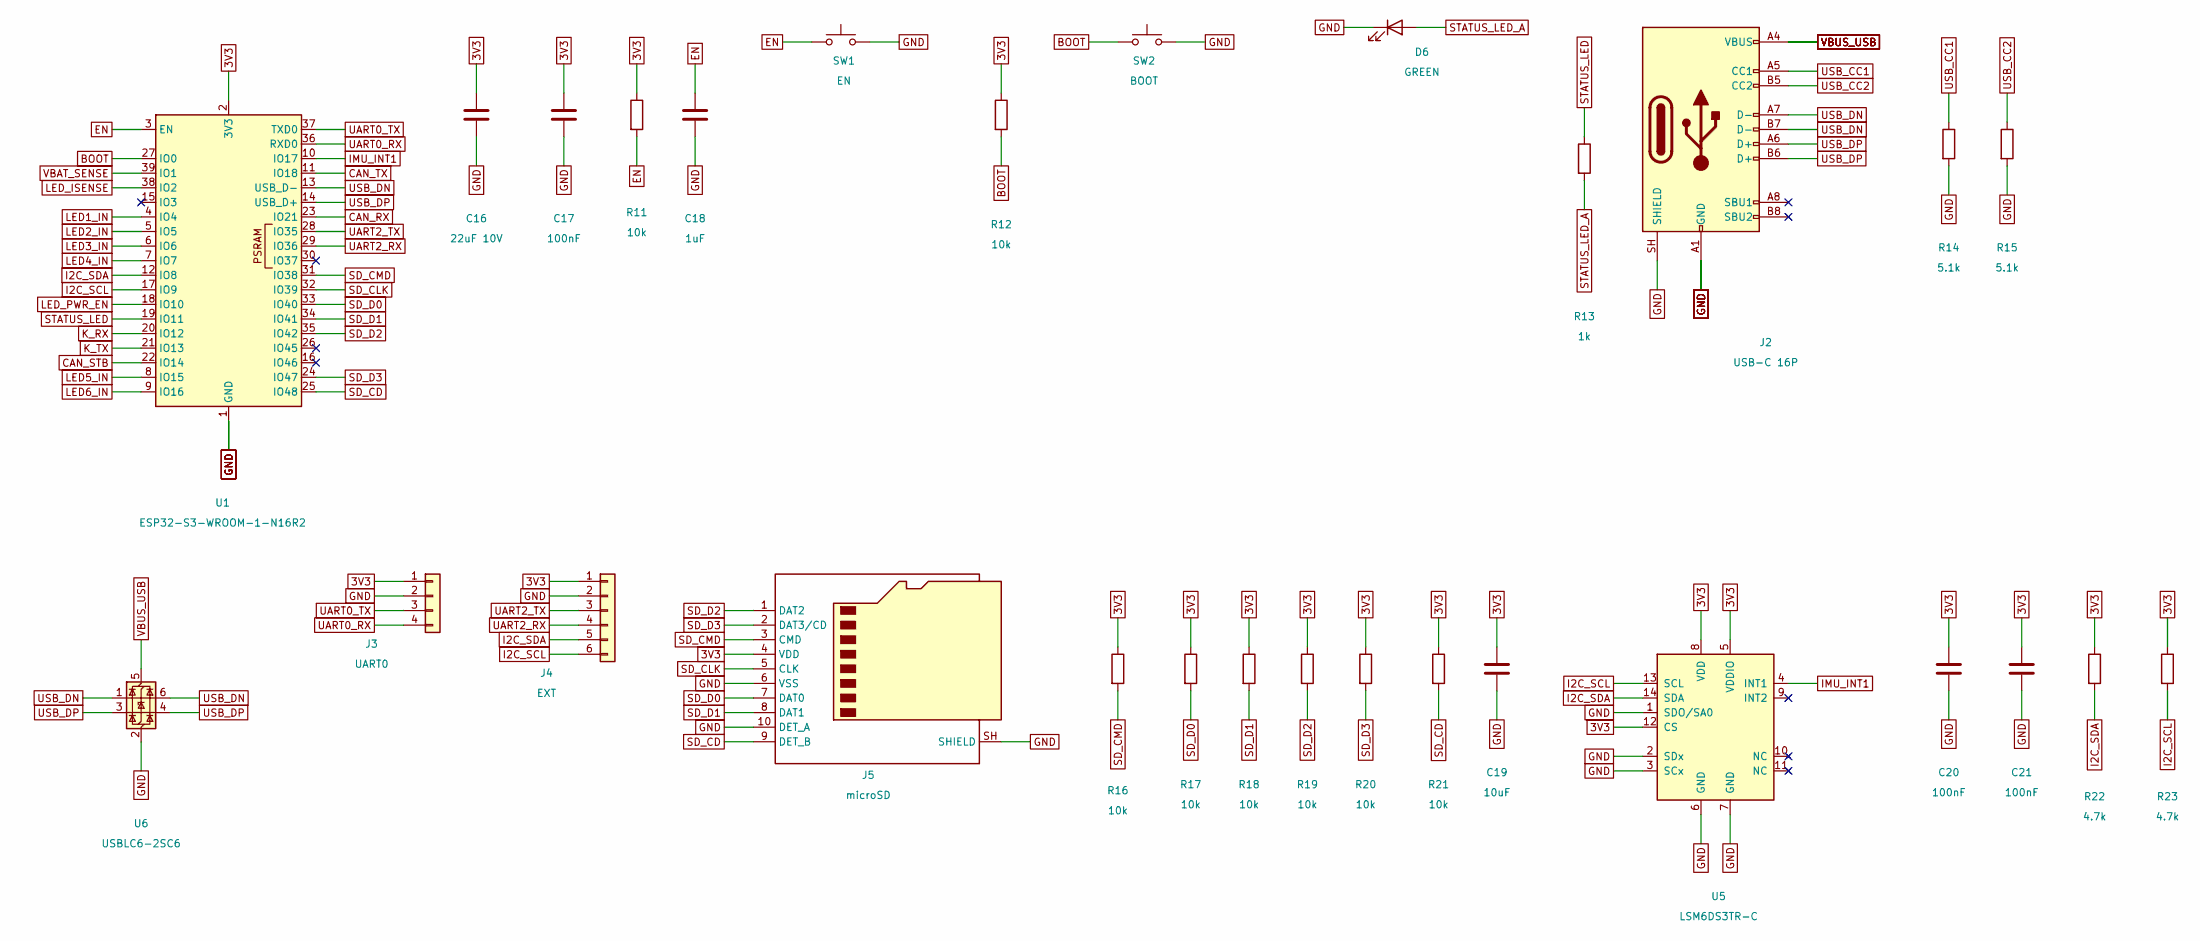
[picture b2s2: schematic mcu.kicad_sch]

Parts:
C16: 22uF 10V; C_0805_2012Metric; MPN CL21A226MAQNNNE; LCSC C45783
C17, C20, C21: 100nF; C_0603_1608Metric; MPN CC0603KRX7R9BB104; LCSC C14663
C18: 1uF; C_0603_1608Metric; MPN CL10A105KB8NNNC; LCSC C15849
C19: 10uF; C_0805_2012Metric; MPN CL21A106KAYNNNE; LCSC C15850
D6: GREEN; LED_0603_1608Metric; MPN PSC-1608U49GC-G4; LCSC C22371299
J2: USB-C 16P; USB_C_Receptacle_HRO_TYPE-C-31-M-12; MPN TYPE-C 16PIN 2MD(073); LCSC C2765186
J3: UART0; PinHeader_1x04_P2.54mm_Vertical; MPN PZ254V-11-04P; LCSC C2691448
J4: EXT; PinHeader_1x06_P2.54mm_Vertical; MPN PZ254V-11-06P; LCSC C492405
J5: microSD; microSD_HC_Hirose_DM3BT-DSF-PEJS; MPN DM3BT-DSF-PEJS; LCSC C597972
R11, R12, R16, R17, R18, R19, R20, R21: 10k; R_0603_1608Metric; MPN 0603WAF1002T5E; LCSC C25804
R13: 1k; R_0603_1608Metric; MPN 0603WAF1001T5E; LCSC C21190
R14, R15: 5.1k; R_0603_1608Metric; MPN 0603WAF5101T5E; LCSC C23186
R22, R23: 4.7k; R_0603_1608Metric; MPN 0603WAF4701T5E; LCSC C23162
SW1: EN; SW_SPST_PTS645Sx43SMTR92; MPN PTS645SM43SMTR92LFS; LCSC C221880
SW2: BOOT; SW_SPST_PTS645Sx43SMTR92; MPN PTS645SM43SMTR92LFS; LCSC C221880
U1: ESP32-S3-WROOM-1-N16R2; ESP32-S3-WROOM-1; MPN ESP32-S3-WROOM-1-N16R2; LCSC C2913205
U5: LSM6DS3TR-C; LGA-14_3x2.5mm_P0.5mm_LayoutBorder3x4y; MPN LSM6DS3TR-C; LCSC C967633
U6: USBLC6-2SC6; SOT-23-6; MPN USBLC6-2SC6; LCSC C7519

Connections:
3V3: C16.1, C17.1, C19.1, C20.1, C21.1, J3.1, J4.1, J5.4 (VDD), R11.1, R12.1, R16.1, R17.1, R18.1, R19.1, R20.1, R21.1, R22.1, R23.1, U1.2 (3V3), U5.5 (VDDIO), U5.8 (VDD), U5.12 (CS); also elsewhere on the board
BOOT: R12.2, SW2.1, U1.27 (IO0)
CAN_RX: U1.23 (IO21); also elsewhere on the board
CAN_STB: U1.22 (IO14); also elsewhere on the board
CAN_TX: U1.11 (IO18); also elsewhere on the board
EN: C18.1, R11.2, SW1.1, U1.3 (EN)
GND: C16.2, C17.2, C18.2, C19.2, C20.2, C21.2, D6.1 (K), J2.A1 (GND), J2.A12 (GND), J2.B1 (GND), J2.B12 (GND), J2.SH (SHIELD), J3.2, J4.2, J5.6 (VSS), J5.10 (DET_A), J5.SH (SHIELD), R14.2, R15.2, SW1.2, SW2.2, U1.1 (GND), U1.40 (GND), U1.41 (GND), U5.1 (SDO/SA0), U5.2 (SDx), U5.3 (SCx), U5.6 (GND), U5.7 (GND), U6.2 (GND); also elsewhere on the board
I2C_SCL: J4.6, R23.2, U1.17 (IO9), U5.13 (SCL)
I2C_SDA: J4.5, R22.2, U1.12 (IO8), U5.14 (SDA)
IMU_INT1: U1.10 (IO17), U5.4 (INT1)
K_RX: U1.20 (IO12); also elsewhere on the board
K_TX: U1.21 (IO13); also elsewhere on the board
LED1_IN: U1.4 (IO4); also elsewhere on the board
LED2_IN: U1.5 (IO5); also elsewhere on the board
LED3_IN: U1.6 (IO6); also elsewhere on the board
LED4_IN: U1.7 (IO7); also elsewhere on the board
LED5_IN: U1.8 (IO15); also elsewhere on the board
LED6_IN: U1.9 (IO16); also elsewhere on the board
LED_ISENSE: U1.38 (IO2); also elsewhere on the board
LED_PWR_EN: U1.18 (IO10); also elsewhere on the board
SD_CD: J5.9 (DET_B), R21.2, U1.25 (IO48)
SD_CLK: J5.5 (CLK), U1.32 (IO39)
SD_CMD: J5.3 (CMD), R16.2, U1.31 (IO38)
SD_D0: J5.7 (DAT0), R17.2, U1.33 (IO40)
SD_D1: J5.8 (DAT1), R18.2, U1.34 (IO41)
SD_D2: J5.1 (DAT2), R19.2, U1.35 (IO42)
SD_D3: J5.2 (DAT3/CD), R20.2, U1.24 (IO47)
STATUS_LED: R13.1, U1.19 (IO11)
STATUS_LED_A: D6.2 (A), R13.2
UART0_RX: J3.4, U1.36 (RXD0)
UART0_TX: J3.3, U1.37 (TXD0)
UART2_RX: J4.4, U1.29 (IO36)
UART2_TX: J4.3, U1.28 (IO35)
USB_CC1: J2.A5 (CC1), R14.1
USB_CC2: J2.B5 (CC2), R15.1
USB_DN: J2.A7 (D-), J2.B7 (D-), U1.13 (USB_D-), U6.1 (I/O1), U6.6 (I/O1)
USB_DP: J2.A6 (D+), J2.B6 (D+), U1.14 (USB_D+), U6.3 (I/O2), U6.4 (I/O2)
VBAT_SENSE: U1.39 (IO1); also elsewhere on the board
VBUS_USB: J2.A4 (VBUS), J2.A9 (VBUS), J2.B4 (VBUS), J2.B9 (VBUS), U6.5 (VBUS); also elsewhere on the board

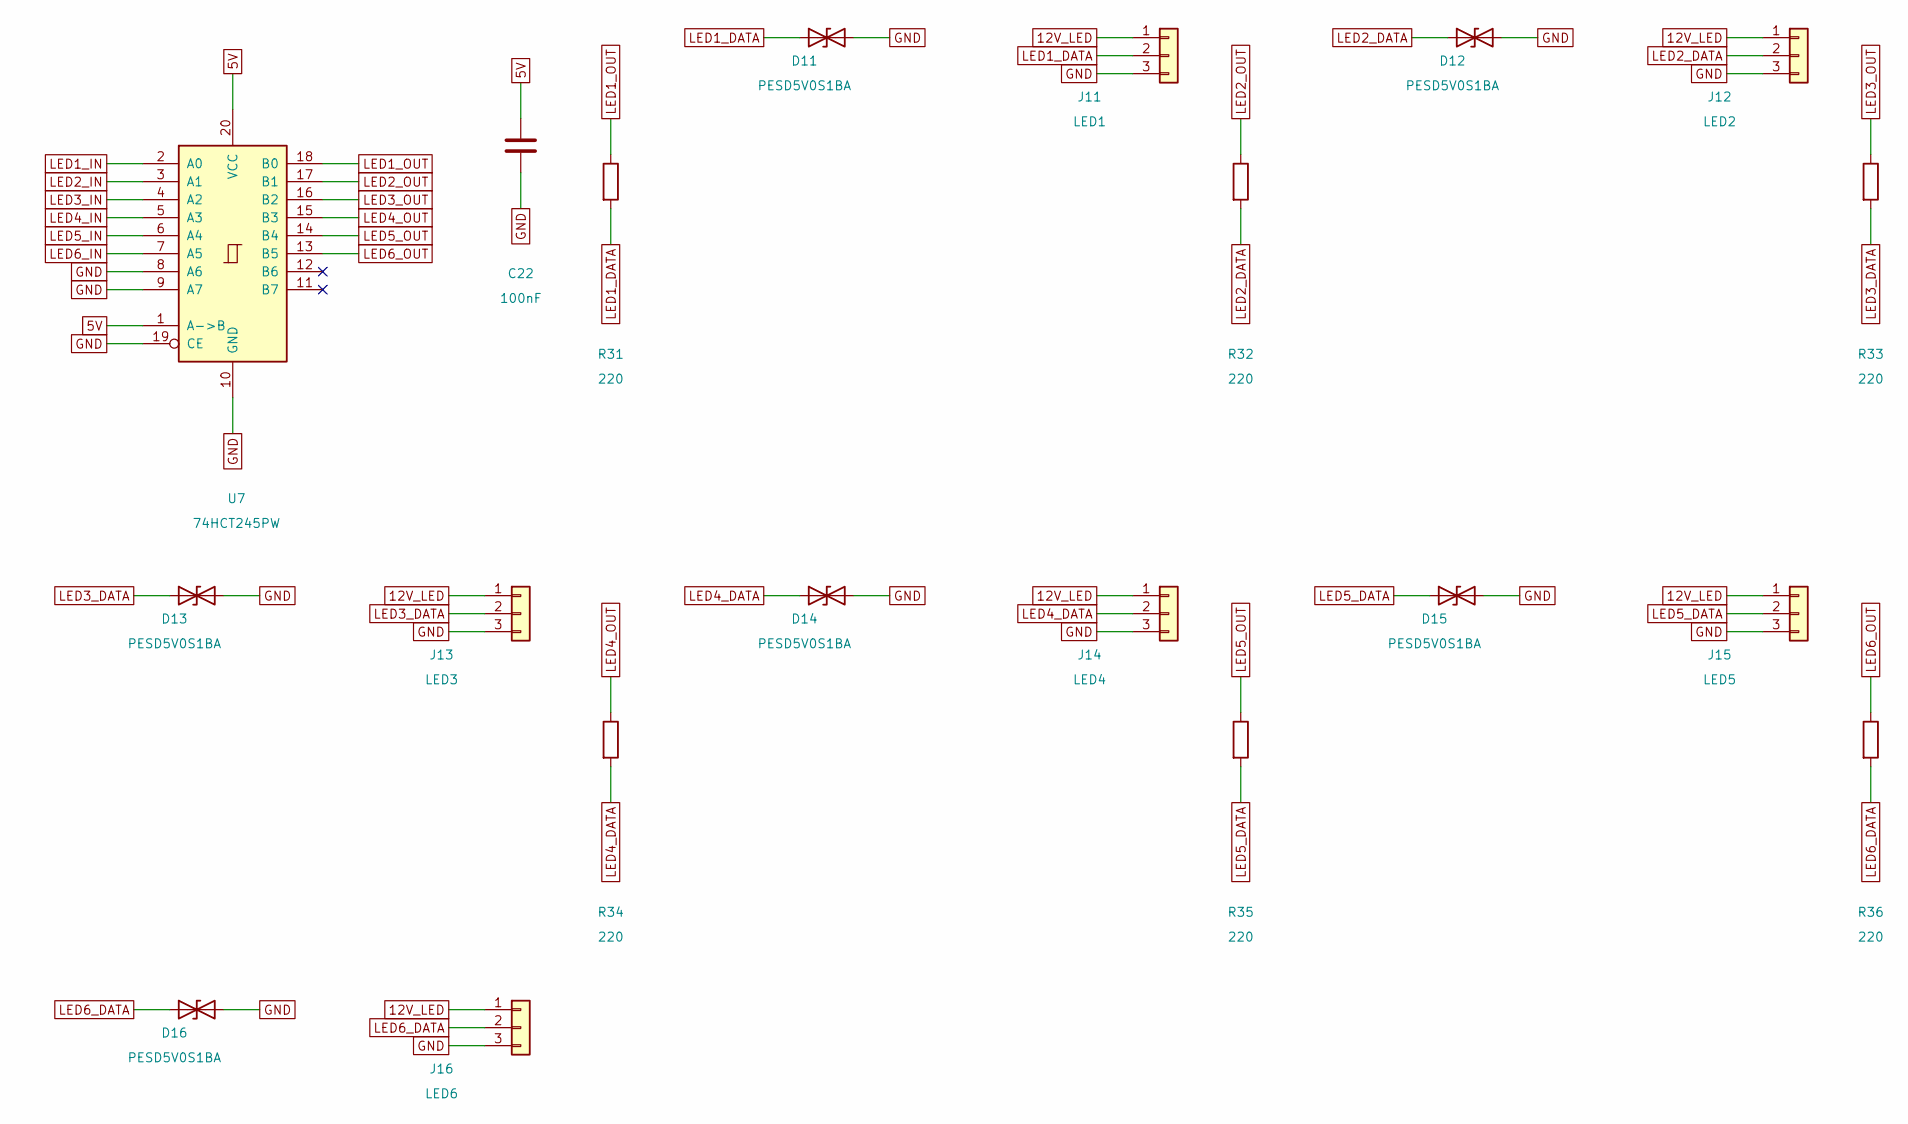
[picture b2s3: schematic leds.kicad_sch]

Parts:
C22: 100nF; C_0603_1608Metric; MPN CC0603KRX7R9BB104; LCSC C14663
D11, D12, D13, D14, D15, D16: PESD5V0S1BA; D_SOD-323; MPN PESD5V0S1BA,115; LCSC C19224
J11: LED1; JST_VH_B3P-VH_1x03_P3.96mm_Vertical; MPN B3P-VH(LF)(SN); LCSC C160316
J12: LED2; JST_VH_B3P-VH_1x03_P3.96mm_Vertical; MPN B3P-VH(LF)(SN); LCSC C160316
J13: LED3; JST_VH_B3P-VH_1x03_P3.96mm_Vertical; MPN B3P-VH(LF)(SN); LCSC C160316
J14: LED4; JST_VH_B3P-VH_1x03_P3.96mm_Vertical; MPN B3P-VH(LF)(SN); LCSC C160316
J15: LED5; JST_VH_B3P-VH_1x03_P3.96mm_Vertical; MPN B3P-VH(LF)(SN); LCSC C160316
J16: LED6; JST_VH_B3P-VH_1x03_P3.96mm_Vertical; MPN B3P-VH(LF)(SN); LCSC C160316
R31, R32, R33, R34, R35, R36: 220; R_0603_1608Metric; MPN 0603WAF2200T5E; LCSC C22962
U7: 74HCT245PW; TSSOP-20_4.4x6.5mm_P0.65mm; MPN 74HCT245PW,118; LCSC C5980

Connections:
5V: C22.1, U7.1 (A->B), U7.20 (VCC); also elsewhere on the board
12V_LED: J11.1, J12.1, J13.1, J14.1, J15.1, J16.1; also elsewhere on the board
GND: C22.2, D11.2 (A2), D12.2 (A2), D13.2 (A2), D14.2 (A2), D15.2 (A2), D16.2 (A2), J11.3, J12.3, J13.3, J14.3, J15.3, J16.3, U7.8 (A6), U7.9 (A7), U7.10 (GND), U7.19 (CE); also elsewhere on the board
LED1_DATA: D11.1 (A1), J11.2, R31.2
LED1_IN: U7.2 (A0); also elsewhere on the board
LED1_OUT: R31.1, U7.18 (B0)
LED2_DATA: D12.1 (A1), J12.2, R32.2
LED2_IN: U7.3 (A1); also elsewhere on the board
LED2_OUT: R32.1, U7.17 (B1)
LED3_DATA: D13.1 (A1), J13.2, R33.2
LED3_IN: U7.4 (A2); also elsewhere on the board
LED3_OUT: R33.1, U7.16 (B2)
LED4_DATA: D14.1 (A1), J14.2, R34.2
LED4_IN: U7.5 (A3); also elsewhere on the board
LED4_OUT: R34.1, U7.15 (B3)
LED5_DATA: D15.1 (A1), J15.2, R35.2
LED5_IN: U7.6 (A4); also elsewhere on the board
LED5_OUT: R35.1, U7.14 (B4)
LED6_DATA: D16.1 (A1), J16.2, R36.2
LED6_IN: U7.7 (A5); also elsewhere on the board
LED6_OUT: R36.1, U7.13 (B5)
